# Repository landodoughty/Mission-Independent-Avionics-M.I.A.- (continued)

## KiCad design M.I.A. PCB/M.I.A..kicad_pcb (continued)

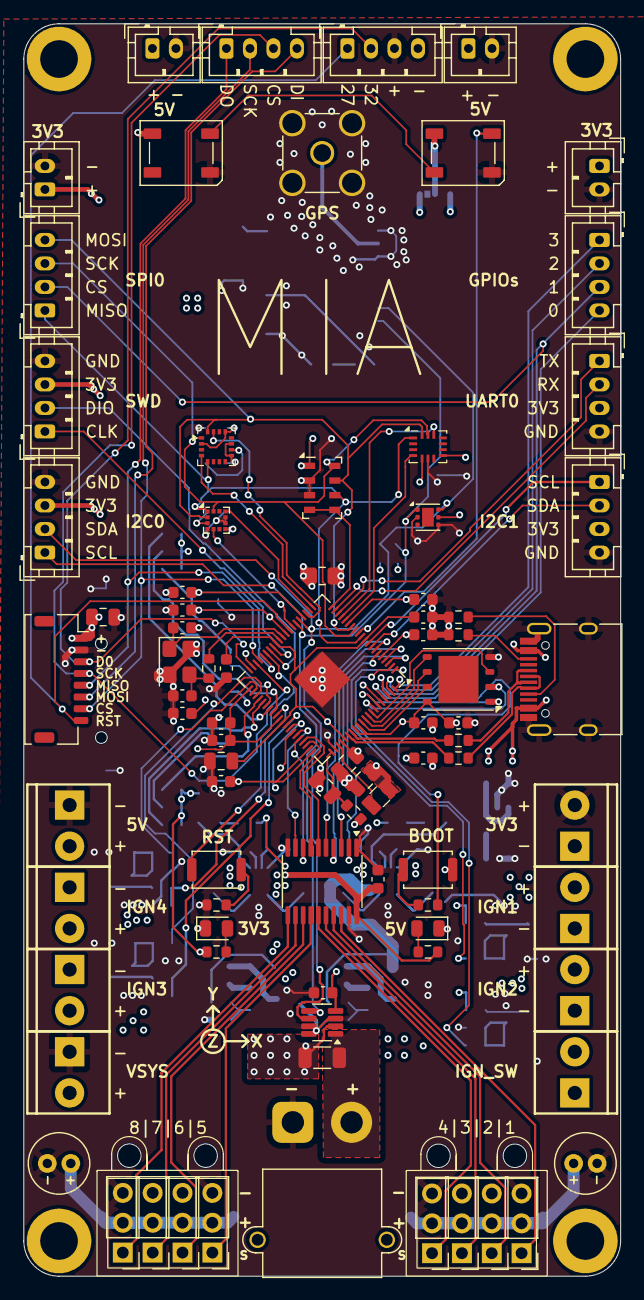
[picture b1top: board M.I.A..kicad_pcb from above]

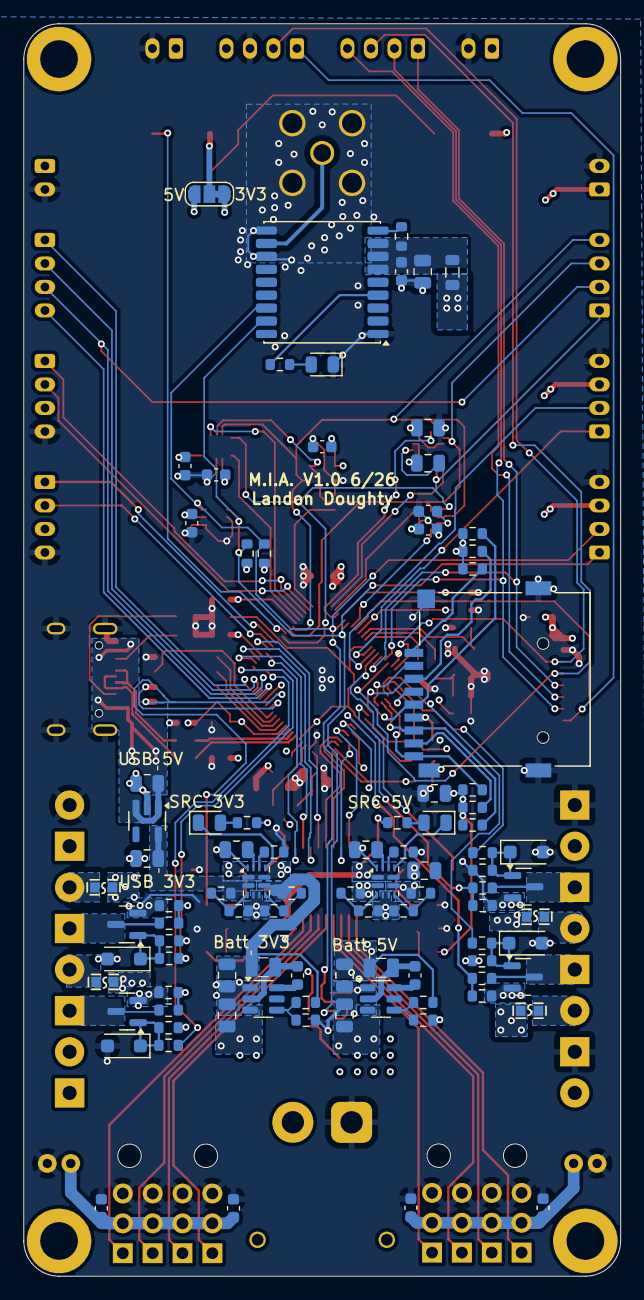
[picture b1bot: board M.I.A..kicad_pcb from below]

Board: 4 copper layers, 50.8 x 106.6 mm, 186 parts (94 on the bottom side), 131 nets.

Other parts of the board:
G1, G2: 3x4PinHeaderCase90deg
G3: orientationIndicator

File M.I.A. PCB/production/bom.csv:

Designator,Footprint,Quantity,Value,LCSC Part #
"C1, C10, C11, C12, C17, C2, C21, C23, C24, C25, C26, C28, C29, C30, C34, C38, C4, C41, C5, C6, C7, C8, C9",0603,23,100n,C1525
"C13, C20, C36, C40, C42",0805,5,10u,C15850
"C14, C15, C16, C27, C3",0805,5,4.7u,C23733
"C18, C19",0603,2,15p,C1548
"C22, C31, C37",0805,3,1u,C28323
"C32, C33",0805,2,1u,C15850
"C35, C39",0805,2,22u,C45783
C43,0805,1,10u,
"C44, C45",C_Radial_D5.0mm_H11.0mm_P2.00mm,2,100u,C15850
"C46, C47, C48, C49",0603,4,100n,C15850
"D1, D2, D3, D4, D5",0805,5,RED_LED,C84256
"D10, D11",LED_WS2812B_PLCC4_5.0x5.0mm_P3.2mm,2,WS2812B,
"D6, D7, D8, D9",D_SOD-123F,4,BZT52Bxx,
"F1, F2, F3, F4",ERBRE3R00V,4,ERBRE3R00V,C713406
FB1,0805,1,120ohm,
"G1, G2",3x4PinHeaderCase90deg,2,3x4PinHeaderCase90deg,
G3,orientationIndicator,1,orientationIndicator,
"H1, H2, H3, H4",MountingHole_3.2mm_M3_ISO14580_Pad,4,MountingHole,
J1,USB_C_Receptacle_HRO_TYPE-C-31-M-12,1,USB_C_Receptacle_USB2.0_16P,
"J10, J11, J14, J15, J16, J17, J7, J8",PinHeader_1x03_P2.54mm_Vertical,8,Conn_01x03,
J12,CUI_MSD-4-A,1,MSD-4-A,
"J13, J18, J19, J24, J26, J28, J6, J9",JST_PH_B4B-PH-K_1x04_P2.00mm_Vertical,8,Conn_01x04_Socket,
J2,SMA_Amphenol_132134-11_Vertical,1,Conn_Coaxial,
"J20, J21, J22, J23, J3, J32, J33, J4",ScrewTerminal_1x02_P3.5mm_Horizontal_Black,8,Screw_Terminal_01x02,
J25,JST_SHL_SM08B-SHLS-TF_1x08-1MP_P1.00mm_Horizontal,1,Conn_01x08_Socket,
"J27, J29, J30, J31",JST_PH_B2B-PH-K_1x02_P2.00mm_Vertical,4,Conn_01x02_Socket,
J5,AMASS_XT30PW-M_1x02_P2.50mm_Horizontal,1,Conn_01x02_Pin,
"L1, L2, L3",AOTA-B201610S3R3-101-T(L_0806_2016metric),3,3.3u,
"Q1, Q2, Q3, Q4",SOT-23,4,AO3400A,
R1,0603,1,33,C25105
"R10, R9",0603,2,5.1k,C25105
"R11, R12, R5",0603,3,1k,C11702
"R13, R17, R4",0603,3,100,C25076
"R14, R32, R33, R34, R35, R36, R37",0603,7,10k,C25744
"R15, R23",0603,2,100k,C25792
"R16, R20, R21, R24, R28, R29",0603,6,100k,C25741
"R18, R27",0603,2,47K,C25741
R19,1206,1,2m,
"R2, R3",0603,2,27,C25092
R22,0603,1,47k,C25792
"R25, R6",0603,2,270,C25076
R26,0603,1,15k,C25756
R30,0603,1,68k,C25792
R31,0603,1,13k,C25756
"R38, R39, R46, R47",0603,4,5M,
"R40, R41, R48, R49",0603,4,1k,
"R42, R44, R50, R52",0603,4,10k,
"R43, R45, R51, R53",0603,4,1M,
"R7, R8",0603,2,4.7k,C25900
"SW1, SW2",SW_Push_SPST_NO_Alps_SKRK,2,SW_Push,
U1,WSON-8-1EP_6x5mm_P1.27mm_EP3.4x4mm,1,W25Q128JVS,C97521
U10,SOT-23-8,1,INA219AxDCN,
U11,SOT-23-5,1,AP2112K-3.3,
"U12, U14",TSOT-23-6,2,AP62150WU,C3194237
"U13, U9",Texas_VQFN-HR-12_2x2.5mm_P0.5mm,2,TPS2121RUXR,C485916
U15,SSOP-20_4.4x6.5mm_P0.65mm,1,74AHC541,
U2,QFN-80-1EP_10x10mm_P0.4mm_EP3.4x3.4mm,1,RP2350B-QFN80,
U3,LGA-16_3x3mm_P0.5mm,1,MMC5983MA,C404329
U4,Bosch_LGA-14_3x2.5mm_P0.5mm,1,ICM-45686,C22459454
U5,LGA-8_3x5mm_P1.25mm,1,MS5611-01BA,C15639
U6,WSON-6-1EP_2x2mm_P0.65mm_EP1x1.6mm,1,TMP117xxDRV,
U7,ublox_MAX,1,MAX-M10S,
U8,LGA-12_2x2mm_P0.5mm,1,KX134-1211,C2157908
Y1,Crystal_SMD_3225-4Pin_3.2x2.5mm,1,ABM8-272-T3,C20625731

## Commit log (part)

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2026-05-25 Add ignore.gitignore for Python Cache and Temporary KiCad files
2026-05-25 Telemetry Display GUI first commit
2026-05-25 Hopefully includes pycache files correctly now
2026-05-25 Delete GroundStationDisplay/__pycache__ directory
    removed pycache files
2026-05-25 these shouldnt commit
2026-05-25 Add .gitignore file
2026-05-25 Added new files for the Ground Station and M.I.A. Code.
2026-05-25 added pcb files
2026-05-26 Started Layout
2026-05-27 Worked on Layout, Changed IMU
2026-05-28 added servo pin protector and changed screw terminal size
2026-05-28 updated LDO and Power Sensor
    may need to change LDO to support power draw of RFM95CW
2026-05-30 Finished Layout other than gps, extra connectors, and ignition lines
2026-06-01 Worked More on Layout/Wiring
2026-06-02 Wired Sensors
2026-06-05 routed continuity sensing and pwm routing fixed
2026-06-10 Routed GPS Maybe Correctly
2026-06-10 Routed two ignition lines
2026-06-12 Added LEDs, Prepped for 4 layer conversion
2026-06-12 6 to 4 layer conversion
2026-06-12 Updated top connectors to be TLM_SPI
2026-06-15 routed ign3/4, fixed some drc
2026-06-16 Final Fixes, impedances, silkscreen etc
2026-06-16 More Small Updates/Improvements
2026-06-25 Likely Final PCB
